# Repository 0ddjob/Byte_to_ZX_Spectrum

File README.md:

# Byte_to_ZX_Spectrum
Converter board for the Belarusian ZX Spectrum clone called the Байт (Byte). <br>
 
This machine has an, ahem, excessive 96-pin connector called an СНП59-96 (SNP59).  This connector has three rows of 32 pins each and is *almost* the same as a DIN41612 connector ... except for the Soviet-era 2.5mm pin pitch (compared to Western 2.54mm).  <br>

So a DIN41612 connector will not work.  That's the first issue.<br>

The second issue is, of course, it's not a Spectrum edge connector so peripherals won't connect anyway.

Special notes "Connecting DivIDE to BYTE":
- Pin A25 from divIDE we connect to byte on which we send out a low romcs signal such as the pin A30:
- Cut pin 4 or 4/5 of the DD67 (555ИД7) chip from ground and solder a resistor (180Ω to 10kΩ)
- Use a cable to lead pin 4 or 4/5 to a free pin of the edge connector, e.g. A30
- ROMCS signal (A25) from DivIDE connect to pin A30

Current status (28-Sept-2023):<br>
- Connectors and test boards have arrived<br>
- Not working with DivMMC - investigating<br>

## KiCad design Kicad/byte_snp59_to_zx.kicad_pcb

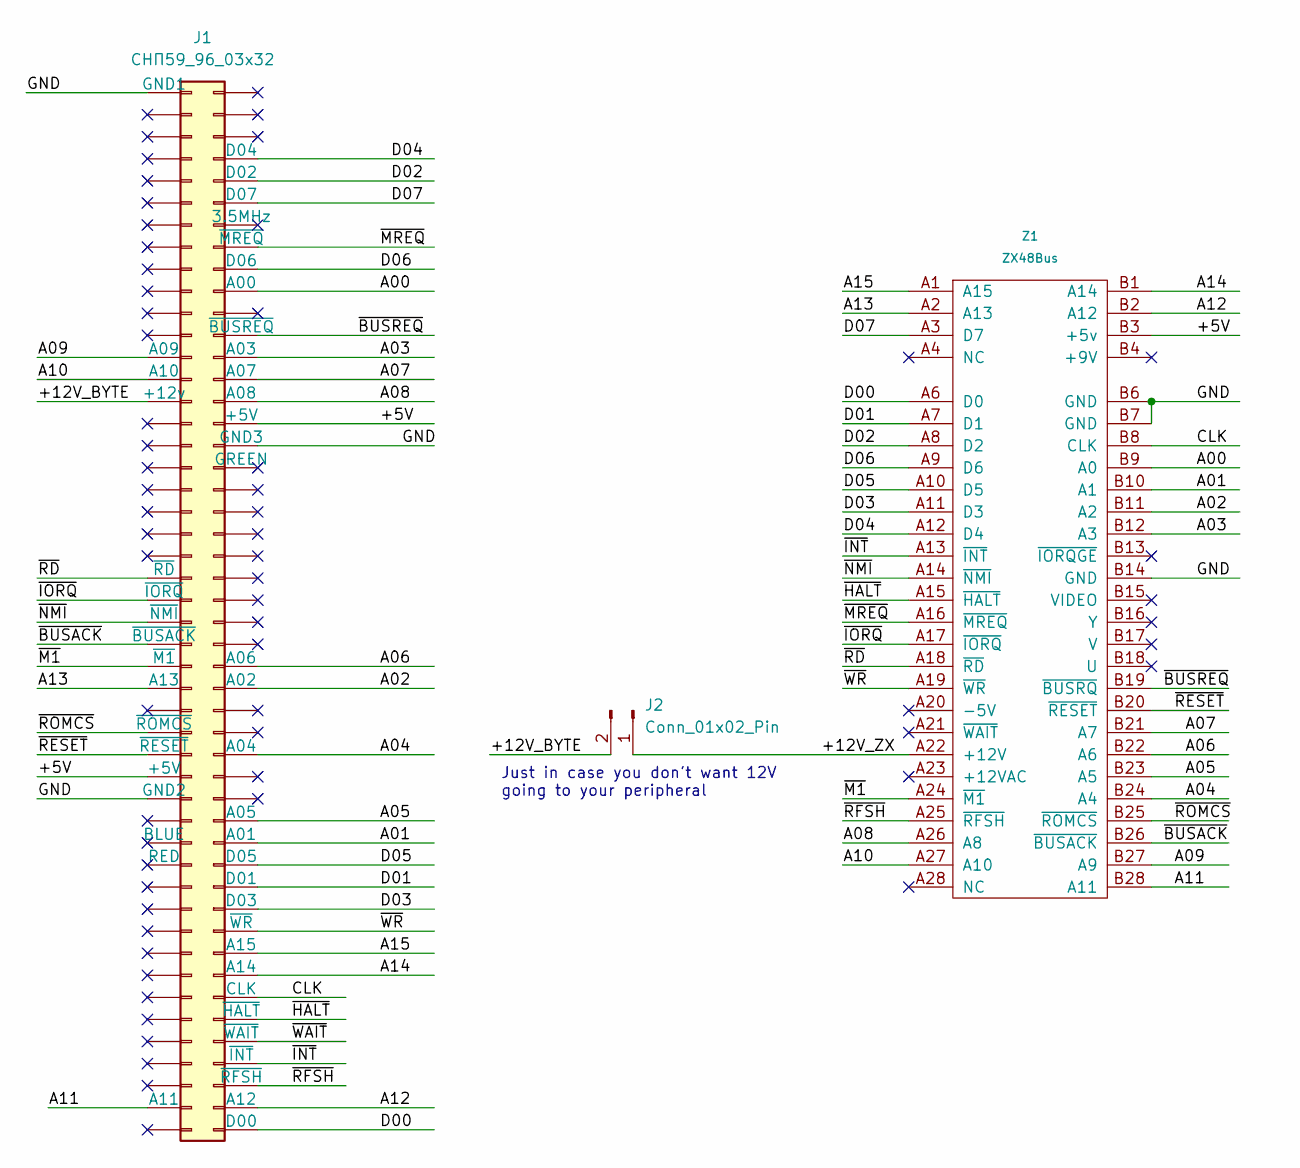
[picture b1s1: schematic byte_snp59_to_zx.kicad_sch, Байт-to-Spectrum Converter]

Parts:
J1: СНП59_96_03x32; SNP59_96_Female
J2: Conn_01x02_Pin; PinHeader_1x02_P2.54mm_Vertical
Z1: ZX48Bus; ZX_Bus_Edge_Connector

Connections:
/+5V: J1.a32 (+5V), J1.b32 (+5V), Z1.B3 (+5v)
/+12V_BYTE: J1.a15 (+12v), J2.2
/+12V_ZX: J2.1, Z1.A22 (+12V)
/A00: J1.b26 (A00), Z1.B9 (A0)
/A01: J1.c19 (A01), Z1.B10 (A1)
/A02: J1.c12 (A02), Z1.B11 (A2)
/A03: J1.b29 (A03), Z1.B12 (A3)
/A04: J1.c15 (A04), Z1.B24 (A4)
/A05: J1.c18 (A05), Z1.B23 (A5)
/A06: J1.c11 (A06), Z1.B22 (A6)
/A07: J1.b30 (A07), Z1.B21 (A7)
/A08: J1.b31 (A08), Z1.A26 (A8)
/A09: J1.a13 (A09), Z1.B27 (A9)
/A10: J1.a14 (A10), Z1.A27 (A10)
/A11: J1.b15 (A11), Z1.B28 (A11)
/A12: J1.c31 (A12), Z1.B2 (A12)
/A13: J1.a28 (A13), Z1.A2 (A13)
/A14: J1.c25 (A14), Z1.B1 (A14)
/A15: J1.c24 (A15), Z1.A1 (A15)
/CLK: J1.c26 (CLK), Z1.B8 (CLK)
/D00: J1.c32 (D00), Z1.A6 (D0)
/D01: J1.c21 (D01), Z1.A7 (D1)
/D02: J1.b21 (D02), Z1.A8 (D2)
/D03: J1.c22 (D03), Z1.A11 (D3)
/D04: J1.b20 (D04), Z1.A12 (D4)
/D05: J1.c20 (D05), Z1.A10 (D5)
/D06: J1.b25 (D06), Z1.A9 (D6)
/D07: J1.b22 (D07), Z1.A3 (D7)
/GND: J1.a1 (GND1), J1.b1 (GND2), J1.c1 (GND3), Z1.B6 (GND), Z1.B7 (GND), Z1.B14 (GND)
/~BUSACK: J1.a26 (~BUSACK), Z1.B26 (~BUSACK)
/~BUSREQ: J1.b28 (~BUSREQ), Z1.B19 (~BUSRQ)
/~HALT: J1.c27 (~HALT), Z1.A15 (~HALT)
/~INT: J1.c29 (~INT), Z1.A13 (~INT)
/~IORQ: J1.a24 (~IORQ), Z1.A17 (~IORQ)
/~M1: J1.a27 (~M1), Z1.A24 (~M1)
/~MREQ: J1.b24 (~MREQ), Z1.A16 (~MREQ)
/~NMI: J1.a25 (~NMI), Z1.A14 (~NMI)
/~RD: J1.a23 (~RD), Z1.A18 (~RD)
/~RESET: J1.a31 (~RESET), Z1.B20 (~RESET)
/~RFSH: J1.c30 (~RFSH), Z1.A25 (~RFSH)
/~ROMCS: J1.a30 (~ROMCS), Z1.B25 (~ROMCS)
/~WAIT: J1.c28 (~WAIT)
/~WR: J1.c23 (~WR), Z1.A19 (~WR)

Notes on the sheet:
Just in case you don't want 12V going to your peripheral

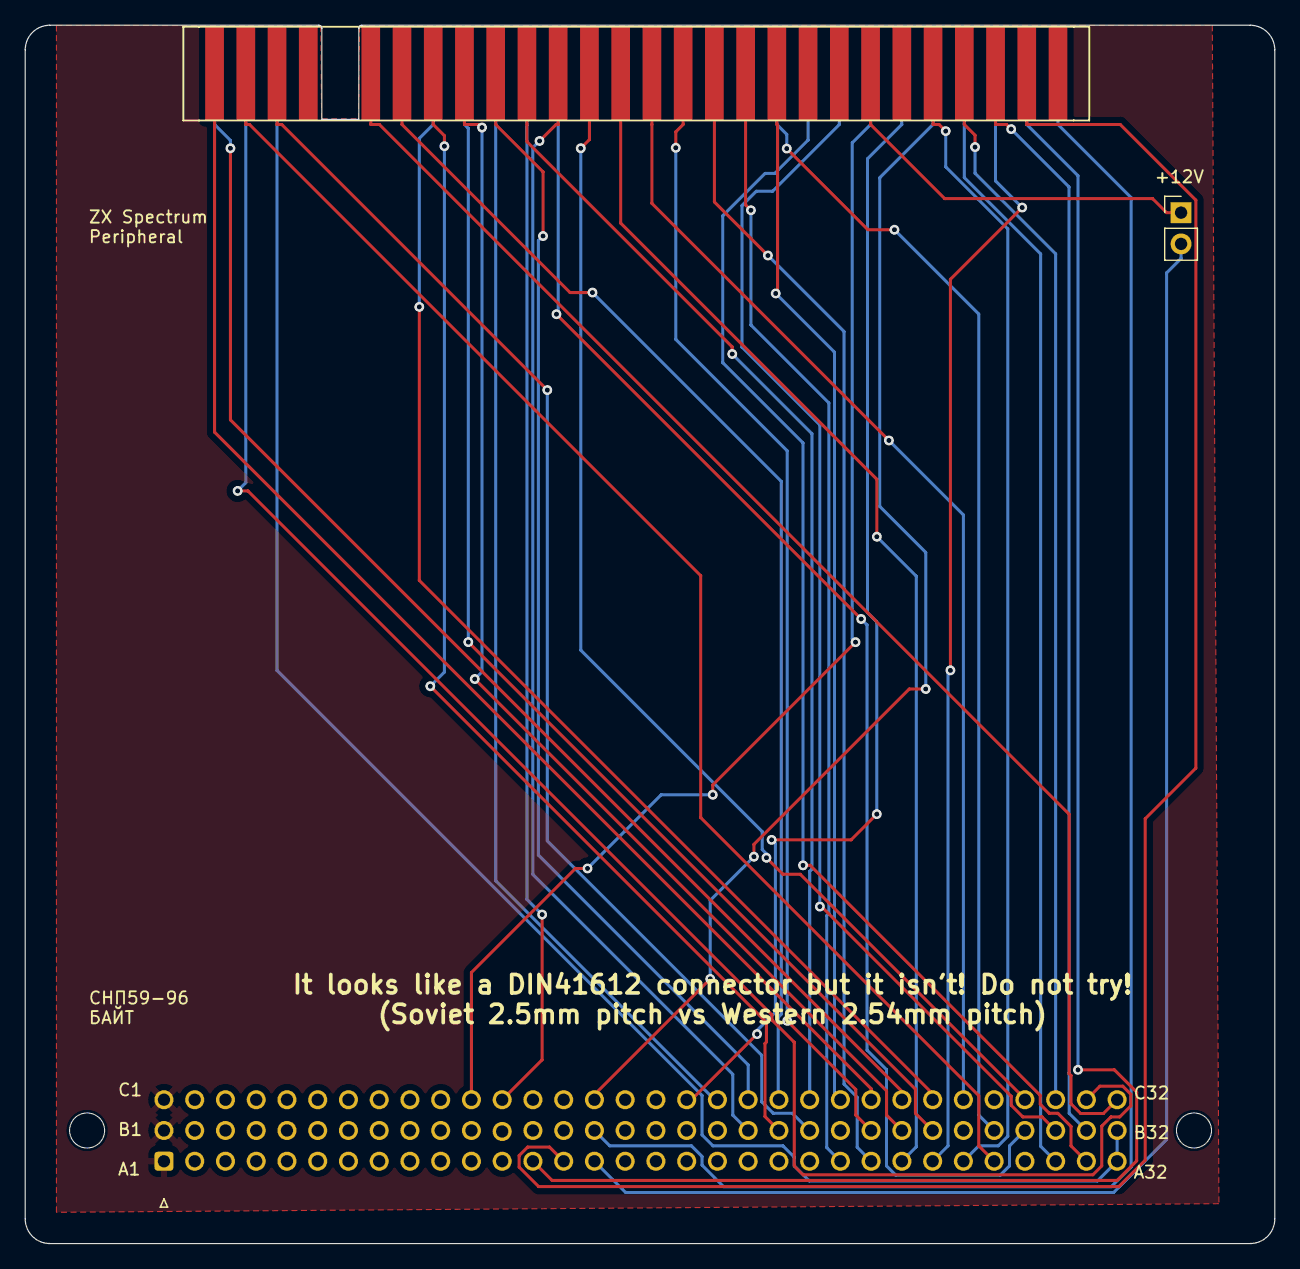
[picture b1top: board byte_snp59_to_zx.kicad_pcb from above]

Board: 2 copper layers, 101.6 x 99.1 mm, 3 parts (0 on the bottom side), 42 nets.

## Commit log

2023-08-28 Connector image
2023-08-29 Initial test design
2023-08-29 Image showing the problem to be solved
    The Bealrusian BYTE computer has an "excessive" 96-pin system bus expansion connector ... with Soviet-era 2.5mm pin pitch.
2023-08-29 extension correction
2023-08-29 Removed space
2023-09-14 Updated PCB text & generated prototype Gerber files
2023-09-16 Update about test fabrication
2023-09-27 New images
